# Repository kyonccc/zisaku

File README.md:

# kataware — 左右無線・トラックボール付き分割キーボード（ZMK 設定）

自作の分割キーボード「kataware」用の ZMK ファームウェア設定です。
基板がまだない段階から使えるように、**「この通りに配線すればこのファームがそのまま動く」**という形で作ってあります。

> この一式は 2026年10月時点の ZMK `main` で、全ファームウェア
> （左手・右手（トラックボール付き）・リセット用）がビルドできることを確認済みです。
> 実物での動作（キー入力・トラックボール）は基板ができてから確認が必要です。

---

## 1. 全体の流れ

自作キーボードは大きく **ハードウェア** と **ファームウェア** の2つに分かれます。

```
[1] 仕様を決める  ← 今ここ（このリポジトリで決めた内容）
[2] 回路図・基板設計（KiCad など）   ← 下の「配線表」に合わせて設計
[3] ケース設計（3Dプリント/アクリル）
[4] 基板・部品の発注、はんだ付け
[5] ファームウェアのビルド・書き込み  ← このリポジトリがそのまま使える
[6] キーマップの調整
```

ファームウェアは「どのピンに何がつながっているか」が決まればほぼ完成します。
**このリポジトリのピン配置に合わせて基板を設計すれば、[5] はすぐ終わります。**

---

> 💡 **部品リスト（寸法・実測欄つき）と確認用の模型**は [docs/parts-list.md](docs/parts-list.md)。
> 💡 **製作用の形は「浮島」**です。データ・買う物・3D プリント・組み立ては **[docs/ukishima-build.md](docs/ukishima-build.md)**、考え方と経緯は [docs/concept/](docs/concept/README.md)。
> このページの「ケース（ガスケットマウント）」の節は古い版の説明です。

## 2. 仕様

| 項目 | 内容 |
| --- | --- |
| 配列 | オーソリニア。片手 5列 × 4段 ＋ **1・2段目の内側に1列（T・G の右／Y・H の左）** ＋ 左手4段目の内側に2キー → **合計46キー**（左24・右22） |
| エンコーダー | **左手**の内側。**英数・Raise キーの真上の中央**に置き、3つで三角形の「塊」にする。回す＋押し込みスイッチ付き。薄型推奨 |
| キー間隔 | 19.05mm（MX と同じ） |
| スイッチ | **Kailh Choc v2（ロープロファイル）・ソケット式**。軸が MX 互換なのでキーキャップを選びやすい |
| トラックボール | **右手に固定**。**25mm（標準）と 19mm を付け替えられる**。センサー PMW3610。右手の内側、**[ ] の列の下・N の段**（カバーの奥の端が ] のすぐ下に来る位置） |
| ボールユニット | **土台（ケースに固定・センサー入り）＋交換カップ（25mm / 19mm）**。ベアリング 681X（外径4mm）3個で支える。PMW3610 基板は土台の底に上向きで置く |
| 基板・ケース | **左右別々の基板**（右手を設計して左右反転し、左右の違いを調整。リバーシブルにはしない）。**ケースは左右同じ大きさ・同じ角の丸み**（外形 約143 × 86mm、角の丸み R14mm、縁 5mm） |
| 接続 | 左右とも完全無線（Bluetooth）。PC とは**右手側**がつながる |
| マイコン | **Seeed Studio XIAO nRF52840 Plus** × 2（**技適取得済み**） |
| 画面 | **nice!view** × 2（左右とも。不要な側は付けなくてよい） |
| 電源 | スライド式の電源スイッチ（左右とも）。持ち運び中は OFF にして電池を節約 |
| リセット | キー操作で書き込みモードに入れる＋キーが効かない時は底板の穴から押す |
| 電池 | リチウムポリマー電池（左右に1個ずつ） |

### トラックボールの付け替え（25mm ⇔ 19mm）

| ボール | 付け方 |
| --- | --- |
| **25mm（標準）** | 土台に **25mm 用カップ**を差し込む |
| **19mm** | 同じ土台に **19mm 用カップ**（アダプター）を差し込む |

- **土台**（センサー入り）はケースの底にネジでとめたまま。**カバーとカップを上から抜いて差し替えるだけ**（ネジを外さない）
- 掃除の時は、どちらのサイズも**カバーを外せばボールだけ上から取り出せる**（ふだんはカバーの縁が押さえていて抜けない）
- どちらのカップも**ボールの一番下の高さが同じ**なので、センサーとのすき間（約2.4mm）は変わらない
- 基板側も**共通**（センサー用コネクタ・センサー PMW3610・ファームウェアは同じ）
- ボールの大きさで動く速さが変わるので、ファームウェアの `cpi`（`kataware_trackball.overlay`）で調整する
- 34mm は浮島で専用の受けを用意した（[浮島の作り方](docs/ukishima-build.md)）

### デザインの方針

- **左右を同じ大きさ・同じ角の丸みの長方形**にして、並べたときに1つの道具に見えるようにする
- 内側の帯（キー2つ分の幅＝38.1mm）は左右で対になる：右は「追加キー2つ＋マイコン＋ボール」、左は「追加キー2つ＋マイコン＋エンコーダー＋親指キー2つ」
- **左の「塊」と右のボールが対になる**（名前の「片割れ」）：左はエンコーダー・英数・Raise の3つを三角形にまとめ、
  右のボールと同じ位置・同じ大きさ感にそろえる。ケースでは、左の塊の台座と右のボールケースを
  同じ素材・同じ色の部品にして、左右で1組に見えるようにする（着せ替えパーツにもできる）
- **ケースとプレートは着せ替えできる作り**にする（素材違いのプレートへの交換、色違いケースなど）
- 飾りは足さず、面取り・角の丸み・素材の色で整える
- 外周は **R14mm** の大きめの角丸（これ以上大きくすると角のキーキャップにかかる）

### 打鍵感をケースで良くする（ロープロファイルでも打ち心地を捨てない）

| 工夫 | 効果 | kataware での扱い |
| --- | --- | --- |
| **ガスケットマウント** | プレートをゴムやポロン（柔らかいスポンジ）で上下から挟んで浮かせる。底打ちが柔らかく、音も静かになる | **浮島で採用**：トレイの柱 8 本の上のポロンに基板を乗せ、下から留める（[作り方](docs/ukishima-build.md)） |
| **プレートの素材を選べるようにする** | FR4（標準・ほどよくしなる）／POM（柔らかく静か）／アルミ（硬くカチッとした感触） | プレートを**交換式**にする（着せ替えの考え方） |
| **フォームを入れる** | プレートと基板の間・基板とケース底の間にスポンジを入れ、カチャカチャした響きを抑える | 底側は XIAO と電池の場所を避けて切り抜く |
| **フレックスカット** | プレートに細い切れ込みを入れて、しなりを足す | プレートの図面に後から追加できる |
| **ケースの重さ・剛性** | 底に薄い金属板を入れて重くすると、ずれにくく、響きも締まる | 持ち運びとの兼ね合いで、薄いステンレス板を検討 |
| **ゴム足** | 机の上で滑らない・響きを吸収 | 底板に付ける |

1台目のおすすめ：**FR4 プレート＋ガスケットマウント＋フォーム**。後からプレートだけ POM などに替えて好みを探す。

### ボールの位置

```
 Q    W    E    R    T    -                 [    Y    U    I    O    P
 A    S    D    F    G    '                 ]    H    J    K    L    ;
 Z    X    C    V    B   (◎)          （●）     N    M    ,    .    /
 Sft  Tab  Ctl Lower Spc 英数 Raise               Enter Raise BS  かな Sft
```

- ボール（●）は右手の **[ ] の列の下、N の段の高さ**。左手のエンコーダー（◎）と左右で向かい合う
- カバーの奥の端が **] のキーのすぐ下**（すき間 約1mm）まで来る
- これ以上は動かせない限界の位置にしてある（`pcb/ergogen/config.yaml` の `ball_x` / `ball_y`）

| ぶつかりそうな部品 | すき間 |
| --- | --- |
| ] のキーキャップ（上） | 約1.1mm |
| N・Enter のキーキャップ（右） | 約1.1mm |
| XIAO（基板の裏・左上） | 約0.7mm（XIAO を 1.5mm 上へずらした） |
| nice!view（左上） | 約1.1mm |

- ボールユニットがケースの内側に収まったので、右手のケースの壁のふくらみがなくなり、**左右のケースが同じ形**になった
- センサーのケーブルは、土台の**右側（Enter の方）**から出して、基板の裏の **コネクタ J**（H と J のキーの下あたり。ソケットのあいだの空き）に挿す

### ボールユニット（土台＋交換カップ）

ボールユニットは、**土台**（ケースに固定）・**カップ**・**カバー**（どちらもボールの大きさごとに差し替え）でできています。

> 浮島では、土台をトレイの床に落とし込み（耳を床の裏から 3 本のネジで留める）、カバーは低い「爪留め」になります。34mm は専用の受けです。
> カップ・ベアリング・ネジでの調整はこの節と同じ。違う所は [浮島の作り方](docs/ukishima-build.md) と [構想のページ](docs/concept/README.md)。

| 部品 | 中身 |
| --- | --- |
| 土台 | 外径 34mm・高さ 13.5mm。**ケースの底に裏から皿ネジ M2 × 3本**（土台の柱に熱圧入インサート M2）。底のくぼみに PMW3610 の基板を置く。奥にケーブルの出口と、カップの向きを決める切り欠き |
| カップ（25mm 用 / 19mm 用） | 土台に差し込むだけ。**ベアリング3個**（120°間隔・0° / 120° / 240°。外側に 1 個置くので、キーボードを傾けて（テンティング）も約 45° までボールが浮かない）でボールを下から支える。下の4本の足でセンサー基板を押さえる。奥の「キー」が土台の切り欠きに入り、回らない |
| カバー（25mm 用 / 19mm 用） | **親指で使う向きに 25° 傾けた**押さえ。縁の穴はボールより少し小さい（25mm 用 23.4mm・19mm 用 17.4mm）ので、ふだんはボールが抜けない。**ひねってロックする（バヨネット式）**ので、指が当たっても外れない。外す時は反時計回りに 30° 回すだけ（工具なし） |
| ベアリング | **681X**（内径1.5 × 外径4 × 幅2mm）、3個／カップ。軸は **M1.4 × 6mm のなべタッピングネジ**。**ネジの締め具合で回り方を調整できる**（下の「ボールの回り方の調整」） |
| センサー | PMW3610 の基板（16 × 20mm を想定・**実物合わせ**）。レンズの上面からボールまで **2.4mm** |

- **ガスケットでもボールが動かない理由**：基板とプレートは押すと上下に少し動くが、土台はケースの底にネジでとまっている。
  基板・プレートの穴は直径36mm（ユニット34mm＋まわり1mm）なので、どこにも触れない
- センサーと基板をつなぐケーブルは、少したるませる（基板が動いても引っぱらない）
- 掃除：①カバーを反時計回りに 30° 回して外す ②ボールを取り出す ③ベアリングの表面やカップの中をふく（ベアリングは付けたままで OK） ④ボールをのせ、カバーを差し込んで時計回りに 30° ひねる
- サイズの付け替え：①カバーとボールを外す ②カップをつまんで上に抜く ③もう一方のカップを、奥のキーを合わせて差し込む ④ボールとカバーを付ける
- 高さ（机から）：25mm ボールのてっぺん **約35.5mm**／19mm は **約29.5mm**。カップの上面は 18.5mm（上ケースより 2mm 上）、その上にカバー
- 3D データは `case/stl/ball_base.stl`・`ball_cup_25.stl`・`ball_cup_19.stl`・`ball_cover_25.stl`・`ball_cover_19.stl`。作り直しは `python3 case/ball_unit.py`

#### カバーのロック（ひねって留める）

- カバーの下に**差し込み部（リング）と3つのツメ**、カップの上面に**入口と溝**がある（瓶のふたや、カメラのレンズと同じ考え方）
- 付け方：①カバーを差し込める向きに合わせて上から入れる ②**時計回りに 30° ひねる** → 最後に小さな山を越えて**カチッ**と止まる
  - ツメは**不等間隔**（0°・110°・235°）なので、差し込める向きは1つだけ。ロックすると、カバーの低い側が自動的に親指の方を向く
- 外し方：**反時計回りに 30°** 回して持ち上げる。指でボールを転がしても、カバーを上や横から押しても外れない
- カバーの外側に**すべり止めの溝**（36本）があり、つまんでひねりやすい
- ロックの固さ（カチッの強さ）は `case/ball_unit.py` の `DETENT_H`（小さな山の高さ・0.3mm）で調整できる。
  固すぎる時は 0.2mm、ゆるい時は 0.4mm に

#### ボールの回り方の調整（ネジ式）

- ベアリングは**上からカップの溝に入れ**、カップの**外側の穴から M1.4 × 6mm のネジ**を差して、ベアリングの穴を通し、反対側の下穴にねじ込む
- ベアリングの左右のすき間は 0.15mm と小さくしてあるので、ネジを締めるとネジ頭が壁を押し、**壁がベアリングを軽く挟む**
  - **ゆるめる** → 軽く回るが、ボールがカタカタする（ガタが出る）
  - **締める** → ガタが減り、しっとり回る。締めすぎると重くなる（引っかかる）
- 調整のしかた：
  1. カバーとボールを外し、カップを土台から抜く
  2. 3本のネジを、止まるところまで回してから **1/4 回転ずつゆるめる**
  3. カップを戻してボールをのせ、指で回して確かめる。3か所の重さがそろうように少しずつ合わせる
- 道具：**精密ドライバー（＋ 0番）**。ネジ頭はカップの外側から 約9〜11mm 奥にあるので、軸の長いものを使う
- ⚠️ 樹脂の下穴にねじ込むので、何度も強く締めたりゆるめたりすると穴がゆるくなる。ゆるくなったら、少し長いネジ（M1.4 × 8mm）にするか、カップを印刷し直す

#### 親指で使うためのカバーの角度

- 親指のふだんの位置は右手の **Enter**。そこから左へ滑らせてボールに乗せる。
  そのため、カバーは**親指の来る向き（Enter の方・少し手前）へ 25° 下がる**形にした（`case/ball_unit.py` の `COVER_TILT`・`THUMB_FROM`）
- **親指側の縁は机から約22mm**（25mm）・約21mm（19mm）で、**キーキャップの上（約21mm）とほぼ同じ高さ**。Enter から段差なしでボールに移れる
- 親指側はボールの**赤道のあたりまで見えている**ので、親指の腹で横からも転がせる
- **奥側は約35mm**（25mm）と高く、ボールのてっぺんの少し下まで包む。親指で押し出しても、ボールが奥へ逃げない「背もたれ」になる
- 角度を変えたい時は `COVER_TILT` を変えて作り直す（目安：20°＝ボールが多く見えてなでやすい、30°＝奥の壁が高く押し込みやすい）
- ⚠️ 実際の手の大きさで感じ方が変わるので、カバーだけ角度違いを何個か印刷して試すのがおすすめ（カバーはひねるだけで付け外しできるので交換が簡単）
- 印刷の向き：土台は底を下、カップは**上の縁を下（裏返し）**にする。ネジの下穴やベアリングの溝は樹脂の種類で太さが変わるので、
  まず1つ印刷して確かめる（`case/ball_unit.py` の `SCREW_PILOT_R`・`BRG_SIDE` などで調整）
- ⚠️ センサー基板の大きさ・レンズの高さは買う基板で違う。届いたら測って `SENSOR_W` `SENSOR_L` `LENS_H` を直す

### 基板のイメージ

`python3 tools/draw_pcb.py docs/images` で作り直せる（位置・外形は `pcb/ergogen/config.yaml` と同じ）。

### ケース（浮島・製作用）

低いトレイの柱 8 本の上のポロンに基板（＋プレート）を乗せ、**基板の裏の M2 ナットにトレイの裏からネジで留める**作り。上からネジは見えない。
トレイの裏に MagSafe メタルリングの溝（テンティング用）。データ・買う物・印刷・組み立ては **[docs/ukishima-build.md](docs/ukishima-build.md)**。

### ケース（旧版：ガスケットマウント）

> ⚠️ 古い版の説明です。データは `case/stl/old_gasket/`。浮島でプレートの耳を無くしたので、今のプレートはこのケースに合いません。

**下ケース**（底と壁）と**上ケース**（枠）の2つに分かれ、その間で**プレートの耳を上下からガスケット（ポロン）で挟む**作りです。
基板はプレートにスイッチでぶら下がるので、プレートと基板はいっしょに浮き、どこもケースに触れません。

| 部分 | 決めたこと |
| --- | --- |
| 外形 | 左右同じ 143.35 × 86.2mm、角 R14、壁 5mm |
| ケースの内側 | キーの範囲ちょうど（133.35 × 76.2mm、角 R5）。左右とも同じ形（ボールユニットは内側に収まる） |
| プレート | 内側より 0.5mm 小さい。**耳（幅8mm）6か所**（上2・下2・左右1ずつ）が壁の溝に 3mm 入る |
| ガスケット | 耳の上と下に1枚ずつ（計12枚／片手）。**ポロン 1.5mm 厚**、約 8 × 2.75mm に切る。上は 0.2mm だけつぶれる |
| 基板 | 内側より 0.75mm 小さい（壁に当たらない）。ソケットのパッドが端まで来る列（右手の一番外側・左手の Raise）だけ、細い帯が壁の溝に入る |
| 基板の「舌」 | 内側の側面に、XIAO の USB-C と電源スイッチを出すための舌（幅6mm）。壁の溝に入る |
| 上ケースの開口 | 内側より 0.75mm 大きい（キーキャップと 約1.3mm あく）。角は R3.5 にして角のキーキャップに当てない |
| 上下ケースの固定 | **M2 なべタッピングネジ（長さ12mm）× 6本／片手**。底から入れ、上ケースの下穴（直径1.7mm）にねじ込む |
| 底板 | 厚さ 2.5mm。電池のくぼみ（1mm）、リセット用の穴、ゴム足（直径10mm）のくぼみ 4か所 |
| ボールユニット | 土台を底から**皿ネジ M2 × 3本**でとめる（上の「ボールユニット」） |

#### 高さ（机から）

| 部分 | 高さ |
| --- | --- |
| 底板の上面 | 2.5mm |
| 基板 | 9.5〜11.1mm（下に 7mm：XIAO・電池・ソケットが入る） |
| 下ケースと上ケースの分かれ目 | 10.6mm（下のガスケットが乗る面） |
| プレート | 12.1〜13.3mm（Choc v2：基板の上面からプレートの上面まで 2.2mm） |
| 上ケースの一番上 | 16.5mm |
| キーキャップの上 | 約21mm（キーキャップによる） |
| ボールのてっぺん | 約35.5mm（25mm）／約29.5mm（19mm） |

#### 作り方・3D プリントの向き

- 3D データ（STL）は `case/stl/old_gasket/`。作り直しは `python3 case/kataware_case.py`（先に Ergogen を実行しておく）
  - 平面の形はすべて Ergogen の DXF から読み込むので、`config.yaml` を変えればケースも追従する
  - 高さやネジ・穴の位置は `case/kataware_case.py` の上の方にまとめてある
  - ボールユニットは `python3 case/ball_unit.py`
- 下ケースは**底を下**に、上ケースは**上面を下（裏返し）**にして印刷すると、サポート材がほぼ要らない
- 注文するなら JLC3DP などの樹脂（レジン）印刷。自分で印刷するなら PLA / PETG で OK
- 組み立て順：下ケース → 下のガスケット → プレート＋基板（スイッチを挿した状態）→ 上のガスケット → 上ケース → 底からネジ
- ⚠️ 寸法は部品の実物合わせが必要な所がある（XIAO のリセットボタンの位置、電源スイッチのレバーの位置、ボールユニット）。
  まず1つ印刷して、実物を入れて確かめる

### なぜこの部品なのか

- **Seeed Studio XIAO nRF52840 Plus**
  - **技適取得済み**（国内販売店のページに認証番号の記載あり）。日本で無線を使うための条件を満たす
  - Bluetooth・電池充電回路を内蔵。ZMK に標準対応（ボード名 `xiao_ble`）。自作キーボードでの使用例も多い
  - 普通の XIAO（11本）より **ピンが多く**、kataware の部品（キー・エンコーダー・トラックボール・画面）を追加部品なしでつなげる
  - 小さい（約 21 × 17.8mm）
  - ⚠️ 普通の XIAO nRF52840 とは**別の製品**。購入時は型番と技適の表示を必ず確認する
- **nice!view（画面）**
  - 電波を出さない表示部品なので技適は関係ない
  - 光らないメモリ液晶で、**消費電力がごくわずか**。無線キーボード向け
  - 右手（PC とつながる側）：Bluetooth の接続先・電池残量・**今のレイヤー**を表示。左手：電池残量・接続状態を表示
- **PMW3610 センサー**
  - 低消費電力で、無線トラックボールの自作でよく使われる定番
  - 単体ではなく「PMW3610 ブレイクアウト基板（センサー＋レンズ付きの小基板）」を買うと簡単です
- **ボールは 25mm**
  - 34mm（大きいトラックボール）より小さく、持ち運び向き。19mm・34mm にも付け替えられる
- **ボールのある右手を PC とつながる側（セントラル）にする理由**
  - センサーのデータを左右間の無線で中継しなくてよいので、遅延が少なく設定も簡単
  - デメリット：右手の電池の減りが早くなる（右手だけ容量の大きい電池にすると◎）

### 技適について

- 無線で使うので、**技適取得済みのマイコン（XIAO nRF52840 Plus）**を使う
- 購入前に、総務省「技術基準適合証明等を受けた機器の検索」で型番と認証番号を確認する
- 電波の強さを上げる設定（`CONFIG_BT_CTLR_TX_PWR_PLUS_8` など）は**使わない**（認証の範囲を超えないように）

### 配列について

キーは全部 19.05mm の格子に**一直線に揃えて**並べます（ずれると押しにくくなるため）。
キーの見た目の位置は `boards/shields/kataware/kataware-layout.dtsi` で決めています。

---

### 実寸テンプレート（印刷して手を置いて確かめる）

[`docs/template/kataware-template.pdf`](docs/template/kataware-template.pdf)（A4 横・左手と右手で2ページ）

- 印刷するときは **「実際のサイズ（100%）」** を選ぶ（「ページに合わせる」はNG）
- 左下の線が **50mm ちょうど** か定規で確かめてから使う
- 外形・キーキャップ（18mm 角の目安）・ボール（25mm）と受け皿（約34mm）・エンコーダーのつまみ（15mm）・nice!view（36 × 14mm）・XIAO（21 × 17.8mm、裏側）の位置が実寸で入っている
- 作り直すとき：`python3 tools/make_template.py docs/template` で HTML を作り、ブラウザで PDF に印刷する

---

## 3. 配線表（基板設計のときに使う一番大事な表）

マイコンは **XIAO nRF52840 Plus**。`D0` などは XIAO の端子名です。
（ ）内は nRF52840 本来のピン名で、ファームウェアの中ではこちらを使っている所もあります。

### 使えるピンと使わないピン

| 端子 | 使う？ | 備考 |
| --- | --- | --- |
| D0〜D10 | ◯ | 表側の端子 |
| D11 (P0.15) / D12 (P0.19) / D13 (P1.01) | ◯ | Plus で増えた端子（裏側） |
| D17 (P1.07) / D18 (P1.05) / D19 (P1.03) | ◯ | Plus で増えた端子（裏側） |
| D14 (P0.09) / D15 (P0.10) | ✕ | NFC 用。保護部品がなく GPIO には不向き |
| D16 (P0.31) | ✕ | 電池電圧の測定に使われている |

> 公式のピン配置図には誤りがあると報告されています。上の表は Seeed 公式の
> ボード定義ファイル（BSP）と、実機での動作確認報告に合わせてあります。

### キーマトリックス

ダイオードの向き：**列(COL) → 行(ROW)**（`col2row`）
つまり、各スイッチの後ろにダイオードを付け、ダイオードの線（カソード）が **ROW 側** を向きます。

| 信号 | ピン | 左手 | 右手 |
| --- | --- | --- | --- |
| ROW0 | D0 | 1段目 | 1段目 |
| ROW1 | D1 | 2段目 | 2段目 |
| ROW2 | D2 | 3段目 | 3段目 |
| ROW3 | D3 | 4段目 | 4段目 |
| 列1 | D4 | 一番外側（Q の列） | 一番内側（Y・H の左の追加キーだけ） |
| 列2 | D5 | W の列 | Y の列 |
| 列3 | D6 | E の列 | U の列 |
| 列4 | D7 | R の列 | I の列 |
| 列5 | D8 | T の列 | O の列 |
| 列6 | D9 | T・G の右の追加キー、エンコーダー押し込み、英数 | P の列（一番外側） |
| 列7 | D10 | 一番内側：親指の段の Raise だけ | （トラックボールに使用） |

- 左手：5列 × 4段 ＋ T・G の右 ＋ 4段目の内側に2キー ＝ 24キー ＋ エンコーダー押し込み（D9 の列 × ROW2）
- 右手：5列 × 4段 ＋ Y・H の左 ＝ 22キー

### ロータリーエンコーダー（左手のみ）

| エンコーダー側 | XIAO 側 | 備考 |
| --- | --- | --- |
| A | D11 (P0.15) | |
| B | D12 (P0.19) | |
| C（共通） | GND | |
| 押し込みスイッチ | ROW2 × D9 の列 | 普通のキーと同じくダイオードを付けてマトリックスにつなぐ |

### トラックボールセンサー PMW3610（右手のみ）

| センサー側 | XIAO 側 | 備考 |
| --- | --- | --- |
| VDD / VIN | 3V3 | ブレイクアウト基板の表記に合わせる |
| GND | GND | |
| SCLK | D10 (P1.15) | |
| SDIO | D13 (P1.01) | データの送受信を1本で行う |
| NCS (CS) | D11 (P0.15) | |
| MOTION | D12 (P0.19) | 動いた時に知らせる割り込み線 |

### nice!view（画面、左右とも同じ）

| nice!view 側 | XIAO 側 |
| --- | --- |
| MOSI（DI） | D17 (P1.07) |
| SCK | D19 (P1.03) |
| CS | D18 (P1.05) |
| VCC | 3V3 |
| GND | GND |

画面を付けない側は、`build.yaml` のその側の `shield:` から `nice_view` を消してください。

### 電源まわり（左右共通）

```
電池＋ ──[スライドスイッチ]── XIAO 裏面の BAT+
電池− ─────────────────── XIAO 裏面の BAT−
```

- **スライドスイッチ**は電池の＋側に入れる。OFF にすると電池が完全に切り離されるので、持ち運び中の消費はほぼゼロになる
- 部品は **水平（横向き）スライドスイッチ Alps SSSS811101**（キーボード用として Typeractive・LCSC などで販売。
  ソケットより背が低い表面実装品）。基板の端に付けて、つまみをケースの側面から出す
  - 同じ形の MSK12C02 でも動作は同じだが、検証済みの部品データがある SSSS811101 にそろえる
  - トグルスイッチはレバーが飛び出してカバンの中で勝手に入りやすく、同じ大きさの物もないので使わない
- ⚠️ この配線だと**スイッチが OFF のときは充電されない**。充電するときは ON にして USB をつなぐ
- スイッチはケースの側面から指で操作できる位置に置く。ON/OFF が見て分かるようにつまみの色を変えると◎

### マイコンまわりの配置

（位置は「基板のイメージ」の図を参照）

- 左右とも、内側の帯（キー1個分の幅）にまとめる
- **XIAO は基板の裏側**に**横向き**で付け、**nice!view は表側**に重ねる（表から画面、裏にマイコン）
  - 画面はプレートの窓から見える（上ケースは枠だけなので、画面の上に板はない）
  - XIAO Plus の追加ピン（D11〜D19）は裏面のパッドなので、基板側にパッドを用意してはんだ付けする
- **USB-C** は**内側の側面**（左右が向かい合う面）に出す。基板の「舌」が壁の溝に入り、側面の穴から挿す
  - ケースの角は丸い（R14）ので、奥の角に XIAO を置くと角からはみ出す。そのため横向きにして側面の真ん中寄りに置いた
- **電源スライドスイッチ**も内側の側面の、USB-C の奥側に付ける。レバーは側面の細い穴から爪やペン先で動かす
- **リセットボタン**は XIAO を裏付けすると下向きになるので、**底板の穴から細い棒・ピンで押す**
  （ふだんはキー操作で書き込みモードに入るので、使うのはキーが効かない時だけ）
- 部品の寸法：XIAO nRF52840 Plus は 21 × 17.8mm・厚さ約5mm、nice!view は 36 × 14 × 2.9mm
  - nice!view は縦向きでマイコン用スペース（19.05 × 38.1mm）にぎりぎり収まる（長さ方向の余裕は片側約1mm）
  - 基板の下（XIAO と電池が入る空間）は **7mm**（電池は底板の 1mm のくぼみに入れる）

### リセット（書き込みモードに入る方法）

XIAO のリセットボタンはマイコンの上に付いた小さいボタンなので、ケースに入れると押しにくくなります。
kataware では次の2つを用意します。

1. **キー操作で書き込みモードに入る（ふだんはこちら）**
   - Raise を押しながら、左手なら **T の右のキー**、右手なら **Y の左のキー** → その側が書き込みモードになる
   - Raise を押しながら、その下のキー（G の右 / H の左）→ 再起動
2. **底板の穴から押す（ファームウェアが壊れた時など、キーが効かない時用）**
   - XIAO を基板の裏に付けるので、リセットボタンは下向きになる
   - 底板のボタンの真下に小さな穴をあけ、細い棒やピンで押す。**素早く2回押す**と書き込みモード
   - 押し棒を底板に仕込んでおけば、指で押せるようにもできる
   - マイコンの位置と穴を合わせるので、基板設計の時にボタンの位置を正確に決める

### 電池（リチウムポリマー）の選び方

**方針：販売する・しないに関わらず、PSE マーク付きで、届出事業者名が表示された国内流通品を指定する。**

| 条件 | 内容 |
| --- | --- |
| PSE マーク＋届出事業者名 | 表示があるもの（ジイエクサ Gexa の PSE 認証済みリポを候補にする） |
| 保護回路 | 過充電・過放電・過電流の保護回路付き |
| 厚さ | **5mm 以下**（底板の 1mm のくぼみ＋基板の下のすき間 7mm に入れるため。ソケットとの間に約1mm 残す） |
| 容量 | 左右とも 250mAh（GA-011） |
| コネクタ | 電池側に合わせる（Gexa は 1.25mm ピッチ・PicoBlade 互換と思われる） |

**採用：左右とも ジイエクサ Gexa GA-011（軽さ優先）**

| 項目 | 内容 |
| --- | --- |
| 型番 | Gexa GA-011（PSE 認証済み・保護回路内蔵） |
| 容量 | 250mAh |
| 大きさ | 約 20 × 30 × 5mm（幅 × 長さ × 厚さ） |
| 重さ | 約 6g |
| コネクタ | 1.25mm ピッチ 2ピン（白・ロック爪なし → **Molex PicoBlade 互換と思われる**）。**端子面から見て 左＝黒（−）／右＝赤（＋）** |

- 左右同じ電池にして、仕入れを1種類にする。左右の重さもそろう
- 持ち時間の目安：右手（PC とつながる側＋トラックボール）より左手の方が長持ち（実物で要測定）
- もっと長持ちさせたい時の予備案：GA-012（500mAh・約 30 × 48 × 4mm・約 12g）。同じコネクタなので基板はそのまま使える
- キーの下の空いたスペースに置く（XIAO の真下とボールの穴は避ける）
- 基板側は **Molex PicoBlade 2ピン（横から挿すタイプ・`53261-0271`）**（パッド1＝−、パッド2＝＋）。差し込み口は電池のある方を向く
- ⚠️ 実物の電池を挿して**テスターで＋/−を確認**してから XIAO につなぐ（逆だと XIAO が壊れる）。
  逆だった時は `pcb/ergogen/config.yaml` の電池の `pos` / `neg` を入れ替えて作り直す

- PSE の対象は「体積エネルギー密度 400Wh/L 以上」のリチウムイオン電池。とても小さい電池は対象外で、
  PSE マークが付いていないこともある。kataware では**安全を優先して PSE マーク付きの物だけ**を使う
- **販売する時**：PSE マークと届出事業者名の表示がある電池を、国内の正規の販売元から仕入れて同梱する。
  電池だけの販売・同梱の可否や、配送（リチウム電池の発送条件）は、販売前に経済産業省の FAQ と配送業者の規約で確認する
- コネクタの＋と−は**メーカーによって逆**のことがある。基板に＋/−を印刷し、接続前にテスターで確認する
- 充電は XIAO に USB をつなげば自動で行われる（電源スイッチは ON にしておく）

---

## 3.5 基板の設計（Ergogen で作った下書き）

`pcb/ergogen/` に、キーの位置・外形・穴・部品の置き場所をまとめた **Ergogen の設定**があります。
ここから基板（KiCad 用）とプレート（ケース・板の図面）の下書きを自動で作れます。

### 作り直し方

```
npx ergogen@4.1.0 pcb/ergogen -o pcb/ergogen/output
```

### できるもの（`pcb/ergogen/output/`）

| ファイル | 中身 |
| --- | --- |
| `pcbs/left.kicad_pcb` / `pcbs/right.kicad_pcb` | 基板の下書き。KiCad で開いて配線する |
| `outlines/plate_left.dxf` / `plate_right.dxf` | Choc v2 用プレート（スイッチを固定する板・穴 13.8mm 角）の図面。浮島用（耳・ネジ穴なし） |
| `outlines/pcb_*.dxf` | 基板の外形（右手はボールの穴あり） |
| `outlines/board_*.dxf` | ケースの外形（左右同じ 143.35 × 86.2mm、角 R14） |
| `outlines/cavity_*.dxf` / `top_opening_*.dxf` | ケースの内側・（旧版の）上ケースの開口（ケースの 3D データが読み込む） |

### スイッチは Choc に絞った理由

MX と Choc のソケットを同じキーに置くと、**穴どうし・穴とはんだパッドが重なる**ため、
1枚の基板に両方は載せられません。持ち運び重視なので **Choc（ロープロファイル）に絞りました**。
スイッチは **Choc v2** に決定。Choc v2 は中心の足が太いので、基板の中心の穴は **5.0mm** です
（Choc v1 は挿せません）。

### 部品は本物のデータに置き換え済み

| 部品 | フットプリント（KiCad のライブラリ名） | 元データ |
| --- | --- | --- |
| XIAO nRF52840 Plus（基板の裏・横向き） | `Seeed_Studio_XIAO_Series:XIAO-nRF52840-Plus-SMD` | Seeed Studio 公式（[OPL_Kicad_Library](https://github.com/Seeed-Studio/OPL_Kicad_Library)） |
| 電源スイッチ（Alps SSSS811101 / C&K PCM12） | `Button_Switch_SMD:SW_SPDT_PCM12` | KiCad 標準ライブラリ |
| センサー用コネクタ J（右手の裏） | `Connector_JST:JST_SH_BM06B-SRSS-TB_1x06-1MP_P1.00mm_Vertical` | KiCad 標準ライブラリ |
| 電池コネクタ（基板の裏） | `Connector_Molex:Molex_PicoBlade_53261-0271_1x02-1MP_P1.25mm_Horizontal` | KiCad 標準ライブラリ |
| M2 はんだ付けナット（基板の裏・8 か所） | `kataware:SMT_Nut_M2`（パッド φ5・めっき穴 φ2.4） | kataware 用に作成。買う品番に合わせてパッドを調整 |

- 元の `.kicad_mod` は `pcb/ergogen/lib_src/`、Ergogen 用に変換したものは `pcb/ergogen/footprints/lib/`
  （変換は `python3 tools/import_footprints.py`）
- 各ピンのつながり（ネット）は、ファームウェアのピン割り当てどおりに入っている
- **XIAO の電池パッド（BAT+）は XIAO の真下に隠れる**ので、基板のその位置に小さな穴（直径0.7mm）をあけてある。
  XIAO をはんだ付けした後、**基板の表側からこの穴にはんだを流し込む**（nice!view を付ける前に）
- 簡単な検査：`python3 tools/check_pcb.py`（パッドどうしの近さ・基板の端からの距離・裏の部品の重なり・電池の上の部品）。KiCad の DRC も必ず行う

### 部品データとライセンス（販売するため）

| フォルダ | 中身 | ライセンス |
| --- | --- | --- |
| `pcb/ergogen/footprints/kataware/` | Choc v2 スイッチ・nice!view・M2 はんだ付けナット | kataware 用に作成。Choc v2 は Ergogen 内蔵（MIT）をもとにしたもの |
| `pcb/ergogen/footprints/lib/`（元は `lib_src/`） | 電源スイッチ・JST SH コネクタ・PicoBlade コネクタ | KiCad 標準ライブラリ（CC-BY-SA 4.0。**作った基板には適用されない例外つき**なので販売できる） |
| 同上 | XIAO nRF52840 Plus | Seeed Studio OPL_Kicad_Library（CC-BY-SA 4.0。商用利用可・**出典の表示が必要**）。データを配る時はこの表の表示を残す |
| `pcb/ergogen/footprints/ceoloide/` | エンコーダー | MIT（[ceoloide/ergogen-footprints](https://github.com/ceoloide/ergogen-footprints)） |
| Ergogen 内蔵 | ダイオード | MIT |

**非営利ライセンス（CC-BY-NC-SA）の部品は使っていない**ので、この基板は販売できる形になっている。
KiCad で追加する部品も、KiCad 標準ライブラリ（設計に使った基板は自由に販売できる）か、
販売可能なライセンスのものを選ぶこと
- **配線（パターン）はまだ**。部品どうしのつながり（ネット）は入っているので、KiCad で線を引く
- トラックボールセンサーへの接続は、基板の裏の **6ピンコネクタ J**（JST SH・1.0mm ピッチ・上から挿すタイプ。H と J のキーの下あたり）。並びは 3V3 / GND / SCLK / SDIO / NCS / MOTION
- 各キーのダイオードは、スイッチの位置決め穴をよけるため、キーの中心から右へ 2mm ずらしてある

**KiCad での仕上げ方は [docs/kicad-guide.md](docs/kicad-guide.md) に手順をまとめています。**

## 4. ファイルの構成と役割

```
zisaku/
├── .github/workflows/build.yml       … GitHub が自動でビルドするための設定
├── build.yaml                        … 何をビルドするか（左・右・リセット）
├── zephyr/module.yml                 … boards/ フォルダを読み込ませるための設定
├── pcb/ergogen/                      … 基板・プレートの下書き（Ergogen）
│   ├── config.yaml                   … キーの位置・外形・部品の置き場所
│   ├── footprints/                   … 追加の部品（ceoloide の部品・置き場所の枠・センサー用コネクタ）
│   └── output/                       … 生成された基板（KiCad）・図面（DXF）
├── case/                             … ケース
│   ├── ukishima.py                   … ★浮島（製作用）の 3D データを作るプログラム
│   ├── concept_ukishima.py           … 浮島の形（寸法）と、イメージ画像用の 3D モデル
│   ├── ball_unit.py                  … ボールユニットの形の元（土台・25mm/19mm カップ）
│   ├── kataware_case.py              … 旧版（ガスケットケース）
│   └── stl/ukishima/                 … 浮島の STL（トレイ・ボールユニット）。旧版は stl/old_gasket/
├── config/
│   ├── west.yml                      … ZMK本体とトラックボールドライバの取得元
│   ├── kataware.keymap               … ★キー配置（一番よく編集するファイル）
│   └── kataware.conf                 … ★スリープ時間などの設定
└── boards/shields/kataware/          … キーボードの「ハードウェア定義」
    ├── Kconfig.shield                … シールド名の登録
    ├── Kconfig.defconfig             … 右手がセントラル、分割、トラックボール有効 など
    ├── kataware.dtsi                 … 左右共通：マトリックス、行ピン
    ├── kataware_left.overlay         … 左手：列ピン、エンコーダー有効化
    ├── kataware_left.conf            … 左手：エンコーダーの設定
    ├── kataware_right.overlay        … 右手：列ピン
    ├── kataware_trackball.overlay    … トラックボール（右手と一緒にビルド）
    ├── kataware-layout.dtsi          … キーの見た目上の位置
    └── kataware.zmk.yml              … キーボードの説明情報
```

普段さわるのは **★の2つ** だけです。
`boards/` 以下は基板の配線を変えたときだけ編集します。

---

## 5. ファームウェアの作り方（GitHub Actions）

1. このリポジトリのファイルを編集して push する
2. GitHub のリポジトリ画面で **Actions** タブを開く
3. 数分待ってビルドが ✅ になったら、そのビルドを開いて下の方の
   **Artifacts** から `firmware` をダウンロード
4. zip を解凍すると次の3つが入っています

| ファイル | 書き込む場所 |
| --- | --- |
| `kataware_left.uf2` | 左手 |
| `kataware_right-trackball.uf2` | 右手（トラックボール付き） |
| `settings_reset.uf2` | 設定リセット用（左右共通） |

---

## 6. 書き込み方法

1. キーボードを USB で PC につなぐ
2. **書き込みモードにする**：Raise ＋ 内側の追加キー（左は T の右、右は Y の左）を押す。
   キーが効かない時は底板の穴からリセットボタンを**素早く2回押す** → PC に `XIAO-SENSE` などのドライブが現れる
3. 「5. ファームウェアの作り方」の表どおりの `.uf2` をそのドライブにドラッグ＆ドロップ
4. 自動で再起動したら完了。反対側も同じように書き込む
5. PC の Bluetooth 設定で **「kataware」** を探してペアリング

### 左右がつながらない時

1. 左右両方に `settings_reset…uf2` を書き込む
2. 左右両方に、もう一度それぞれのファームを書き込む
3. 左右両方の電源を一度 OFF → ON にする（または底板の穴からリセットボタンを押す）
4. PC 側の Bluetooth 登録も一度削除してから、再ペアリング

---

## 7. 初期キーマップ

```
 Q    W    E    R     T     -                    [     Y     U     I    O    P
 A    S    D    F     G     '                    ]     H     J     K    L    ;
 Z    X    C    V     B    (◎)              ●          N     M     ,    .    /
 Sft  Tab  Ctl  Lower Space 英数 Raise                 Enter Raise BS   かな  Sft
```

- **Ctl**：タップで Esc、長押しで Ctrl
- **英数**：タップで 英数、長押しで GUI（Windows キー / Mac の Command）
- **かな**：タップで かな、長押しで Alt（Mac の Option）
- **◎ エンコーダー**：回すと音量（Lower 中はページ送り、Raise 中は画面の明るさ）、押すとミュート

| レイヤー | 入り方 | 内容 |
| --- | --- | --- |
| 0 Base | 通常 | QWERTY |
| 1 Lower | 左の Lower を押している間 | 数字、矢印、Home/End/PageUp/PageDown、Delete、` と ' |
| 2 Raise | 左右どちらかの Raise を押している間 | 記号、F1〜F12、Bluetooth 切替 |
| 3 Mouse | **ボールを動かすと自動で ON**（約0.7秒で OFF） | 右手 J/K/L、左手 F/D/S がクリック |
| 4 Scroll | Mouse 中に `;`（右）か `A`（左）を押している間 | ボールでスクロール |

- Bluetooth は Raise レイヤーの 2段目左から「接続先0〜4」、4段目の左内側が「接続先の削除」です。
  スマホ・PC など最大5台を切り替えられます。
- 英数/かなは Mac では確実に動作、Windows は IME の設定次第です。

---

## 8. よくあるカスタマイズ

### キーの割り当てを変える
`config/kataware.keymap` の `&kp Q` などを書き換えます。
キーの名前一覧：https://zmk.dev/docs/keymaps/list-of-keycodes

### カーソルの速さを変える
`boards/shields/kataware/kataware_trackball.overlay` の `cpi = <600>;` を変更（200〜3200、200刻み）。
大きいほど速くなります。

### カーソルの向きがおかしい
同じファイルの `// swap-xy;` `// invert-x;` `// invert-y;` の `//` を外して調整します。
センサーをケースにどの向きで付けたかで変わるので、実物で試しながら決めます。

### スクロールの向きが逆
`config/kataware.keymap` の `scroller` の部分を次のように変えます。
```
input-processors = <&zip_xy_to_scroll_mapper &zip_scroll_transform INPUT_TRANSFORM_Y_INVERT &zip_scroll_scaler 1 8>;
```
（ファイル先頭に `#include <dt-bindings/zmk/input_transform.h>` も追加）

### キーボードの名前を変える
`kataware` という文字をすべて新しい名前に置き換え、ファイル名の `kataware` も同じように変えます。
Bluetooth に表示される名前は `Kconfig.defconfig` の `ZMK_KEYBOARD_NAME` です（16文字以内）。

### キーの数を増やす・減らす
次の3か所の数を揃える必要があります。
1. `kataware.dtsi` の `default_transform` の `map`（どのスイッチがどの位置か）
2. `kataware-layout.dtsi` の `keys`（見た目の位置）
3. `kataware.keymap` の各レイヤーの `bindings`（割り当て）

---

## 9. 次にやること（ハードウェア）

1. **部品を決めて買う**（浮島のケースで増える物：ナット・カラー・ネジ・ポロン・メタルリングなどは [浮島の作り方](docs/ukishima-build.md#4-買う物浮島で増える物)）：XIAO nRF52840 Plus ×2、PMW3610 ブレイクアウト、25mm ボール、
   ボール支持用ベアリング 681X（1.5 × 4 × 2mm）＋ 軸用 M1.4 × 6mm なべタッピングネジ ×3組（19mm カップも作るなら ×6組）、nice!view ×2、水平スライドスイッチ Alps SSSS811101 ×2、ロータリーエンコーダー（押し込み付き・薄型）×1、Kailh Choc v2 スイッチ ×46、Choc 用ホットスワップソケット ×46、ダイオード 1N4148W（SOD-123・表面実装・基板の裏）×47、PSE 認証済みリポ電池 Gexa GA-011 ×2、1.25mm ピッチ 2ピンコネクタ ×2
2. **キー配置を決める**：[Keyboard Layout Editor](http://www.keyboard-layout-editor.com/) や
   [Ergogen](https://ergogen.xyz/) で配置を決める（Ergogen は配置から基板の下書きまで作れます）
3. **基板設計**：[KiCad](https://www.kicad.org/) で回路図 → 基板。上の配線表どおりにつなぐ
4. **ケース・ボールケース設計**：トラックボールのセンサーとボールの距離（PMW3610 は約2.4mm）が重要
5. **組み立て後**、まずキーだけ → 次にトラックボール、と1つずつ動作確認

---

## 参考

- ZMK 公式ドキュメント：https://zmk.dev/docs
- 新しいキーボードの追加方法：https://zmk.dev/docs/development/hardware-integration/new-shield
- ポインティングデバイス：https://zmk.dev/docs/features/pointing
- PMW3610 ドライバ：https://github.com/badjeff/zmk-pmw3610-driver

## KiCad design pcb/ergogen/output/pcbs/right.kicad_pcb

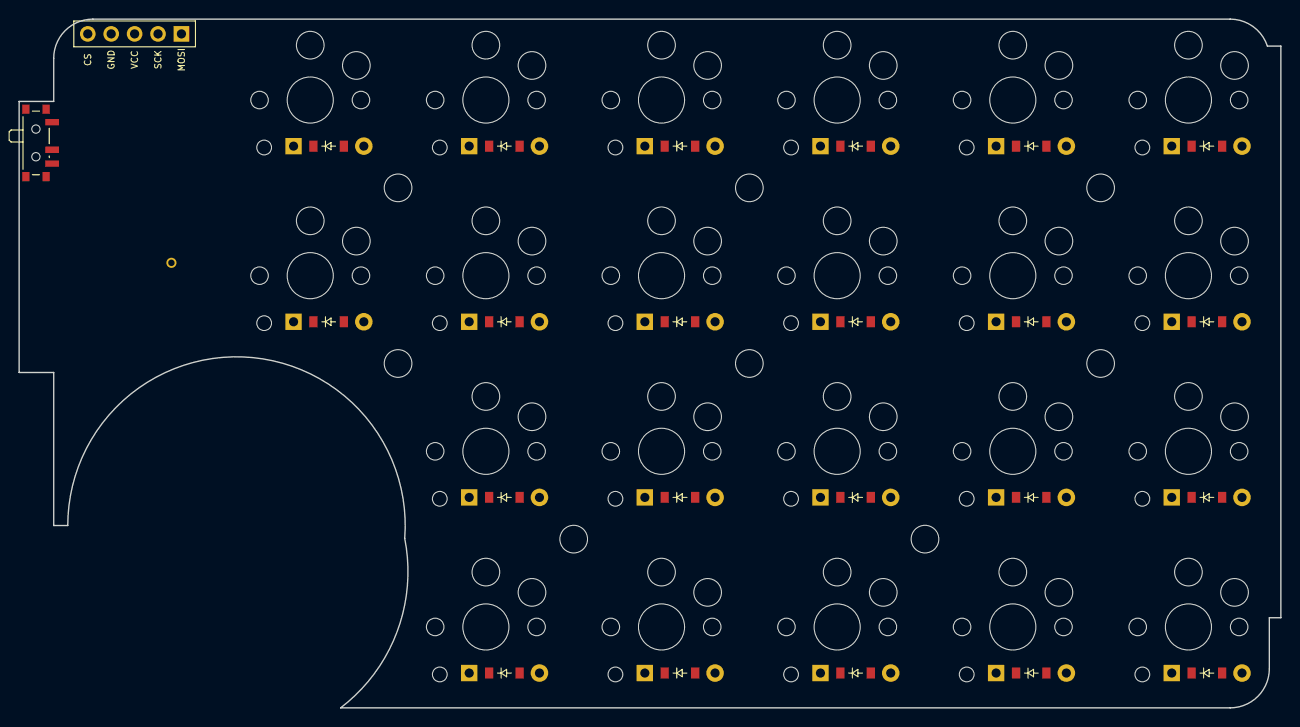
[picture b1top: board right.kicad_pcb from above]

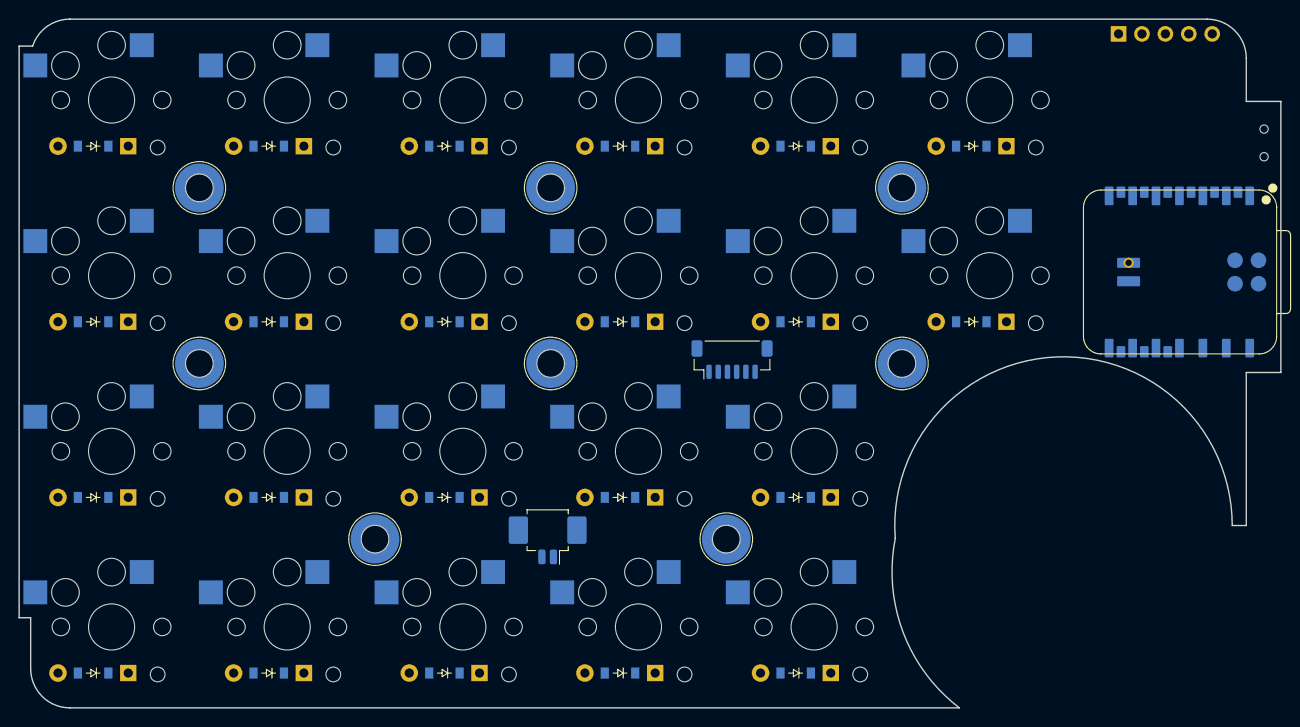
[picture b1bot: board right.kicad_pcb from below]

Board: 2 copper layers, 136.9 x 74.7 mm, 57 parts (11 on the bottom side), 43 nets, no tracks yet.

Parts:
BAT1: Molex_PicoBlade_53261-0271_1x02-1MP_P1.25mm_Horiz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; Molex_PicoBlade_53261-0271_1x02-1MP_P1.25mm_Horizontal
D1, D2, D3, D4, D5, D6, D7, D8, D9, D10, D11, D12, D13, D14, D15, D16, D17, D18, D19, D20, D21, D22: ComboDiode
DISP1: kataware_nice_view
H1, H2, H3, H4, H5, H6, H7, H8: SMT_Nut_M2
J1: JST_SH_BM06B-SRSS-TB_1x06-1MP_P1.00mm_Vertical
MCU1: XIAO-nRF52840-Plus-SMD
PWR1: SW_SPDT_PCM12
S1, S2, S3, S4, S5, S6, S7, S8, S9, S10, S11, S12, S13, S14, S15, S16, S17, S18, S19, S20, S21, S22: kataware_choc_v2_hotswap

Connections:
3V3: DISP1.3, J1.1, MCU1.12
BAT_P: BAT1.2, PWR1.1
BAT_SW: MCU1.28, PWR1.2
COL7: MCU1.5, S1.1, S2.1
COL8: MCU1.6, S3.1, S4.1, S5.1, S6.1
COL9: MCU1.7, S7.1, S8.1, S9.1, S10.1
COL10: MCU1.8, S11.1, S12.1, S13.1, S14.1
COL11: MCU1.9, S15.1, S16.1, S17.1, S18.1
COL12: MCU1.10, S19.1, S20.1, S21.1, S22.1
GND: BAT1.1, DISP1.4, J1.2, MCU1.13, MCU1.27, MCU1.29
ROW0: D2.1, D6.1, D10.1, D14.1, D18.1, D22.1, MCU1.1
ROW1: D1.1, D5.1, D9.1, D13.1, D17.1, D21.1, MCU1.2
ROW2: D4.1, D8.1, D12.1, D16.1, D20.1, MCU1.3
ROW3: D3.1, D7.1, D11.1, D15.1, D19.1, MCU1.4
TB_MOTION: J1.6, MCU1.16
TB_NCS: J1.5, MCU1.15
TB_SCLK: J1.3, MCU1.11
TB_SDIO: J1.4, MCU1.17
VIEW_CS: DISP1.5, MCU1.22
VIEW_MOSI: DISP1.1, MCU1.21
VIEW_SCK: DISP1.2, MCU1.23
right_c8_bottom: D4.2, S4.2
right_c8_home: D5.2, S5.2
right_c8_thumb: D3.2, S3.2
right_c8_top: D6.2, S6.2
right_c9_bottom: D8.2, S8.2
right_c9_home: D9.2, S9.2
right_c9_thumb: D7.2, S7.2
right_c9_top: D10.2, S10.2
right_c10_bottom: D12.2, S12.2
right_c10_home: D13.2, S13.2
right_c10_thumb: D11.2, S11.2
right_c10_top: D14.2, S14.2
right_c11_bottom: D16.2, S16.2
right_c11_home: D17.2, S17.2
right_c11_thumb: D15.2, S15.2
right_c11_top: D18.2, S18.2
right_c12_bottom: D20.2, S20.2
right_c12_home: D21.2, S21.2
right_c12_thumb: D19.2, S19.2
right_c12_top: D22.2, S22.2
right_e_home: D1.2, S1.2
right_e_top: D2.2, S2.2

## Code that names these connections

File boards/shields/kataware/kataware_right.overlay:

/*
 * 右手側 (5列 x 4段 + Y・H の内側に2キー + 内側にトラックボール)
 * kataware_trackball と一緒にビルドする (ボール付き = PCとつながる側)
 */

#include "kataware.dtsi"

// 右手側はキーマップ上で 7列目から始まる (0〜6列目は左手)
&default_transform {
    col-offset = <7>;
};

&kscan0 {
    col-gpios
        = <&xiao_d 4 GPIO_ACTIVE_HIGH>  // COL7  = D4 (一番内側: Y・H の左の追加キーだけ)
        , <&xiao_d 5 GPIO_ACTIVE_HIGH>  // COL8  = D5 (Y H N の列)
        , <&xiao_d 6 GPIO_ACTIVE_HIGH>  // COL9  = D6
        , <&xiao_d 7 GPIO_ACTIVE_HIGH>  // COL10 = D7
        , <&xiao_d 8 GPIO_ACTIVE_HIGH>  // COL11 = D8
        , <&xiao_d 9 GPIO_ACTIVE_HIGH>  // COL12 = D9 (一番外側)
        ;
};

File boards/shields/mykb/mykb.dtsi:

/*
 * mykb 左右共通の定義
 *
 * マイコン: ProMicro nRF52840 互換 (nice!nano v2 等)
 * キー数 : 片手 3行x6列 + 親指3キー = 21キー / 合計42キー
 *
 * ピン番号の `&pro_micro N` は ProMicro の「D番号」です。
 * (例: &pro_micro 4 = D4 ピン)
 */

#include <dt-bindings/zmk/matrix_transform.h>
#include "mykb-layout.dtsi"

// 物理レイアウトとマトリックス変換を結びつける
&mykb_layout {
    transform = <&default_transform>;
};

/ {
    chosen {
        zmk,kscan = &kscan0;
        zmk,physical-layout = &mykb_layout;
    };

    /*
     * マトリックス変換: 「何行目・何列目のスイッチ」が
     * キーマップ上の「何番目のキー」になるかを決める表
     *
     *  左手                                 右手
     * | 0,0 | 0,1 | 0,2 | 0,3 | 0,4 | 0,5 |  | 0,6 | 0,7 | 0,8 | 0,9 | 0,10| 0,11|
     * | 1,0 | 1,1 | 1,2 | 1,3 | 1,4 | 1,5 |  | 1,6 | 1,7 | 1,8 | 1,9 | 1,10| 1,11|
     * | 2,0 | 2,1 | 2,2 | 2,3 | 2,4 | 2,5 |  | 2,6 | 2,7 | 2,8 | 2,9 | 2,10| 2,11|
     *                   | 3,3 | 3,4 | 3,5 |  | 3,6 | 3,7 | 3,8 |
     */
    default_transform: keymap_transform_0 {
        compatible = "zmk,matrix-transform";
        columns = <12>;
        rows = <4>;
        map = <
RC(0,0) RC(0,1) RC(0,2) RC(0,3) RC(0,4) RC(0,5)    RC(0,6) RC(0,7) RC(0,8) RC(0,9) RC(0,10) RC(0,11)
RC(1,0) RC(1,1) RC(1,2) RC(1,3) RC(1,4) RC(1,5)    RC(1,6) RC(1,7) RC(1,8) RC(1,9) RC(1,10) RC(1,11)
RC(2,0) RC(2,1) RC(2,2) RC(2,3) RC(2,4) RC(2,5)    RC(2,6) RC(2,7) RC(2,8) RC(2,9) RC(2,10) RC(2,11)
                        RC(3,3) RC(3,4) RC(3,5)    RC(3,6) RC(3,7) RC(3,8)
        >;
    };

    /*
     * キースキャン(マトリックス配線)
     * diode-direction = "col2row": ダイオードの向きは 列(COL) → 行(ROW)
     * (基板設計時のダイオードの向きと必ず合わせること)
     */
    kscan0: kscan {
        compatible = "zmk,kscan-gpio-matrix";
        wakeup-source;
        diode-direction = "col2row";

        row-gpios
            = <&pro_micro 4 (GPIO_ACTIVE_HIGH | GPIO_PULL_DOWN)>  // ROW0 = D4
            , <&pro_micro 5 (GPIO_ACTIVE_HIGH | GPIO_PULL_DOWN)>  // ROW1 = D5
            , <&pro_micro 6 (GPIO_ACTIVE_HIGH | GPIO_PULL_DOWN)>  // ROW2 = D6
            , <&pro_micro 7 (GPIO_ACTIVE_HIGH | GPIO_PULL_DOWN)>  // ROW3 = D7 (親指)
            ;
        // col-gpios は左右で並び順が違うので各 .overlay に書く
    };

    /*
     * トラックボールの入力リスナー
     * 左右両方のビルドでキーマップから参照できるようにここで定義し、
     * 普段は無効(disabled)。トラックボールがある右手側だけで有効にする。
     */
    trackball_listener: trackball_listener {
        compatible = "zmk,input-listener";
        status = "disabled";
    };
};
